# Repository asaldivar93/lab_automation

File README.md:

## PWM Channels

To control PWM channels you have to create an Output class instance for each channel. The board has up to 6 channels.

```C++
#define N_OUTPUTS 6

Output CH_0(0, PIN_CH0, "pwm", MANUAL, 0);
Output CH_1(1, PIN_CH1, "pwm", MANUAL, 0);
Output CH_2(2, PIN_CH2, "pwm", MANUAL, 0);
Output CH_3(3, PIN_CH3, "pwm", MANUAL, 0);
Output CH_4(4, PIN_CH4, "pwm", MANUAL, 0);
Output CH_5(5, PIN_CH5, "pwm", MANUAL, 0);
Output outputs[N_OUTPUTS] = {CH_0, CH_1, CH_2, CH_3, CH_4, CH_5};
```

Channels can be controled in 4 different modes: {MANUAL, TIMER, PID, ONOFF}. You can initialize this control mode through setter functions.

```C++
Output::set_manual_output(int value);
Output::set_timer(int time_on, int time_off, int value);
Output::set_pid(float *input_value, float setpoint);
Output::set_onoff(float *input_value, int lb, int ub, int value);
```

Example:

```C++
void setup(){
  ...
  outputs[2].set_timer(10, 60, 255);
  ...
}
```

Which is equivalent to doing this:

```C++
void setup(){
  ...
  CH_2.set_timer(10, 60, 255);
  ...
}
```

The PID and ONOFF setters expect a pointer to the measured variable:
```C++
void setup(){
  ...
  outputs[2].set_pid(&inputs[1].value, 50.5);
  outputs[3].set_pid(&inputs[3].value, 1, 1.5, 255);
  ...
}
```
### PID control

The PID controler has important parameters that need to be defined during MCU initialization. This parameters have default values:

- PWM_min_vaule = 0
- PWM_max_value = 255
- Sampling time in microseconds = 250000 (0.250s)
- PID constants:
  - Kp = 100, Ki = 0.2, Kd = 0.

The PID controler uses a simple g-h filter to smooth very noisy signals. The filter uses this formula:

```C++
filtered_input[k] = alpha * current_input + (1 - alpha) * filtered_input[k - 1]
```
where *alpha* [0, 1] controls the strength of the smoothing. *alpha* = 1 **no smoothing at all**, *alpha* close to 0 **very strongth smoothing**. By **default** *alpha* = 0.01.

The default values were tuned to control the temperature of a water reservoir using an external electrical resistance and have been tested to heat water volumes between 50mL and 2L.

These parameters are initialized through setter functions:

```C++
Output::set_sample_time_us(uint32_t sample_time_us);
Output::set_pid_tunings(float Kp, float Ki, float Kd);
Output::set_output_limits(float min, float max);
Output::set_gh_filter(float alpha);
```
example:

```C++
void setup(){
  ...
  outputs[2].set_sample_time_us(250000);
  outputs[2].set_pid_tunings(100, 0.2, 0.);
  outputs[2].set_output_limits(0, 240);
  outputs[2].set_gh_filter(0.01);
  outputs[2].set_pid(&inputs[1].value, 50.5);
  ...
}
```

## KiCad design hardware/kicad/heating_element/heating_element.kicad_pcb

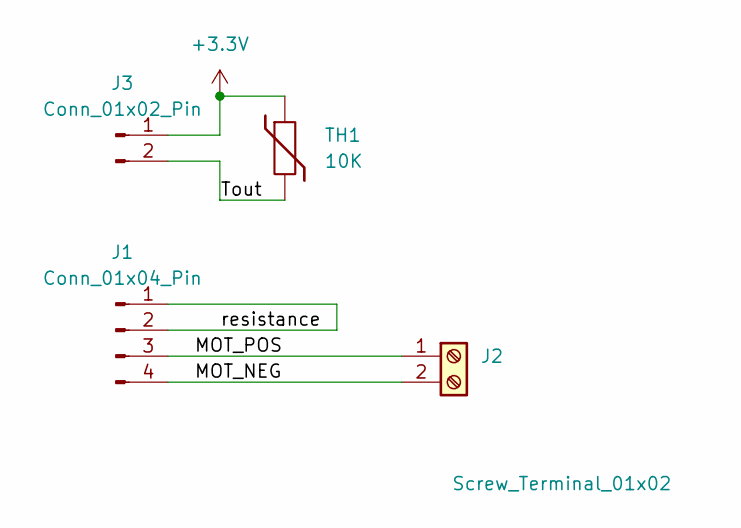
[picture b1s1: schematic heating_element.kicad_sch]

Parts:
J1: Conn_01x04_Pin; PinHeader_1x04_P2.54mm_Vertical
J2: Screw_Terminal_01x02; TerminalBlock_Phoenix_PT-1,5-2-5.0-H_1x02_P5.00mm_Horizontal
J3: Conn_01x02_Pin; PinHeader_1x02_P2.54mm_Vertical
TH1: 10K; R_Axial_DIN0204_L3.6mm_D1.6mm_P1.90mm_Vertical

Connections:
+3.3V: J3.1, TH1.1
/MOT_NEG: J1.4, J2.2
/MOT_POS: J1.3, J2.1
/Tout: J3.2, TH1.2
/resistance: J1.1, J1.2

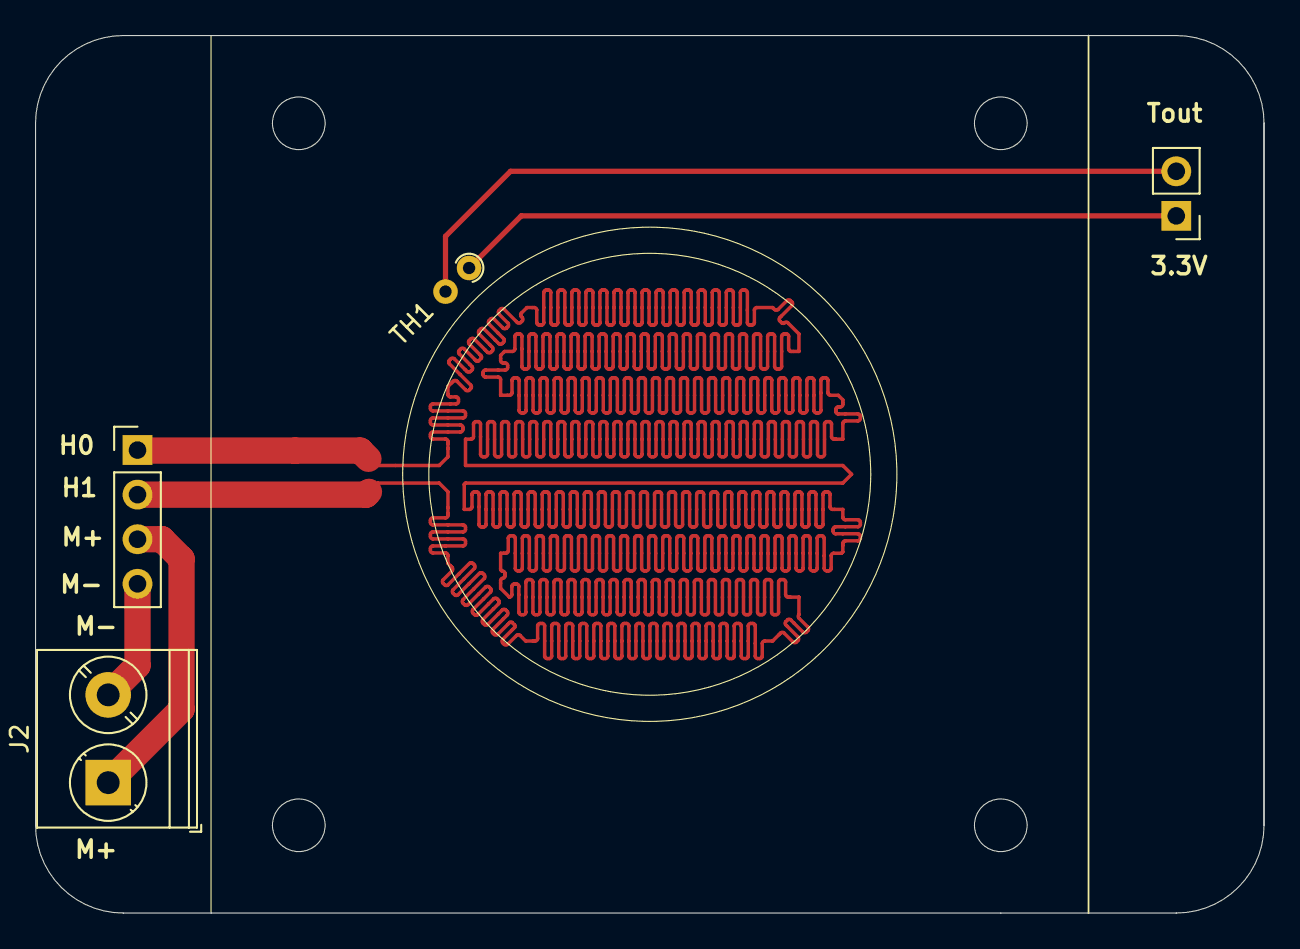
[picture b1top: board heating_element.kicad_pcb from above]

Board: 2 copper layers, 70.0 x 50.0 mm, 4 parts (0 on the bottom side), 5 nets.

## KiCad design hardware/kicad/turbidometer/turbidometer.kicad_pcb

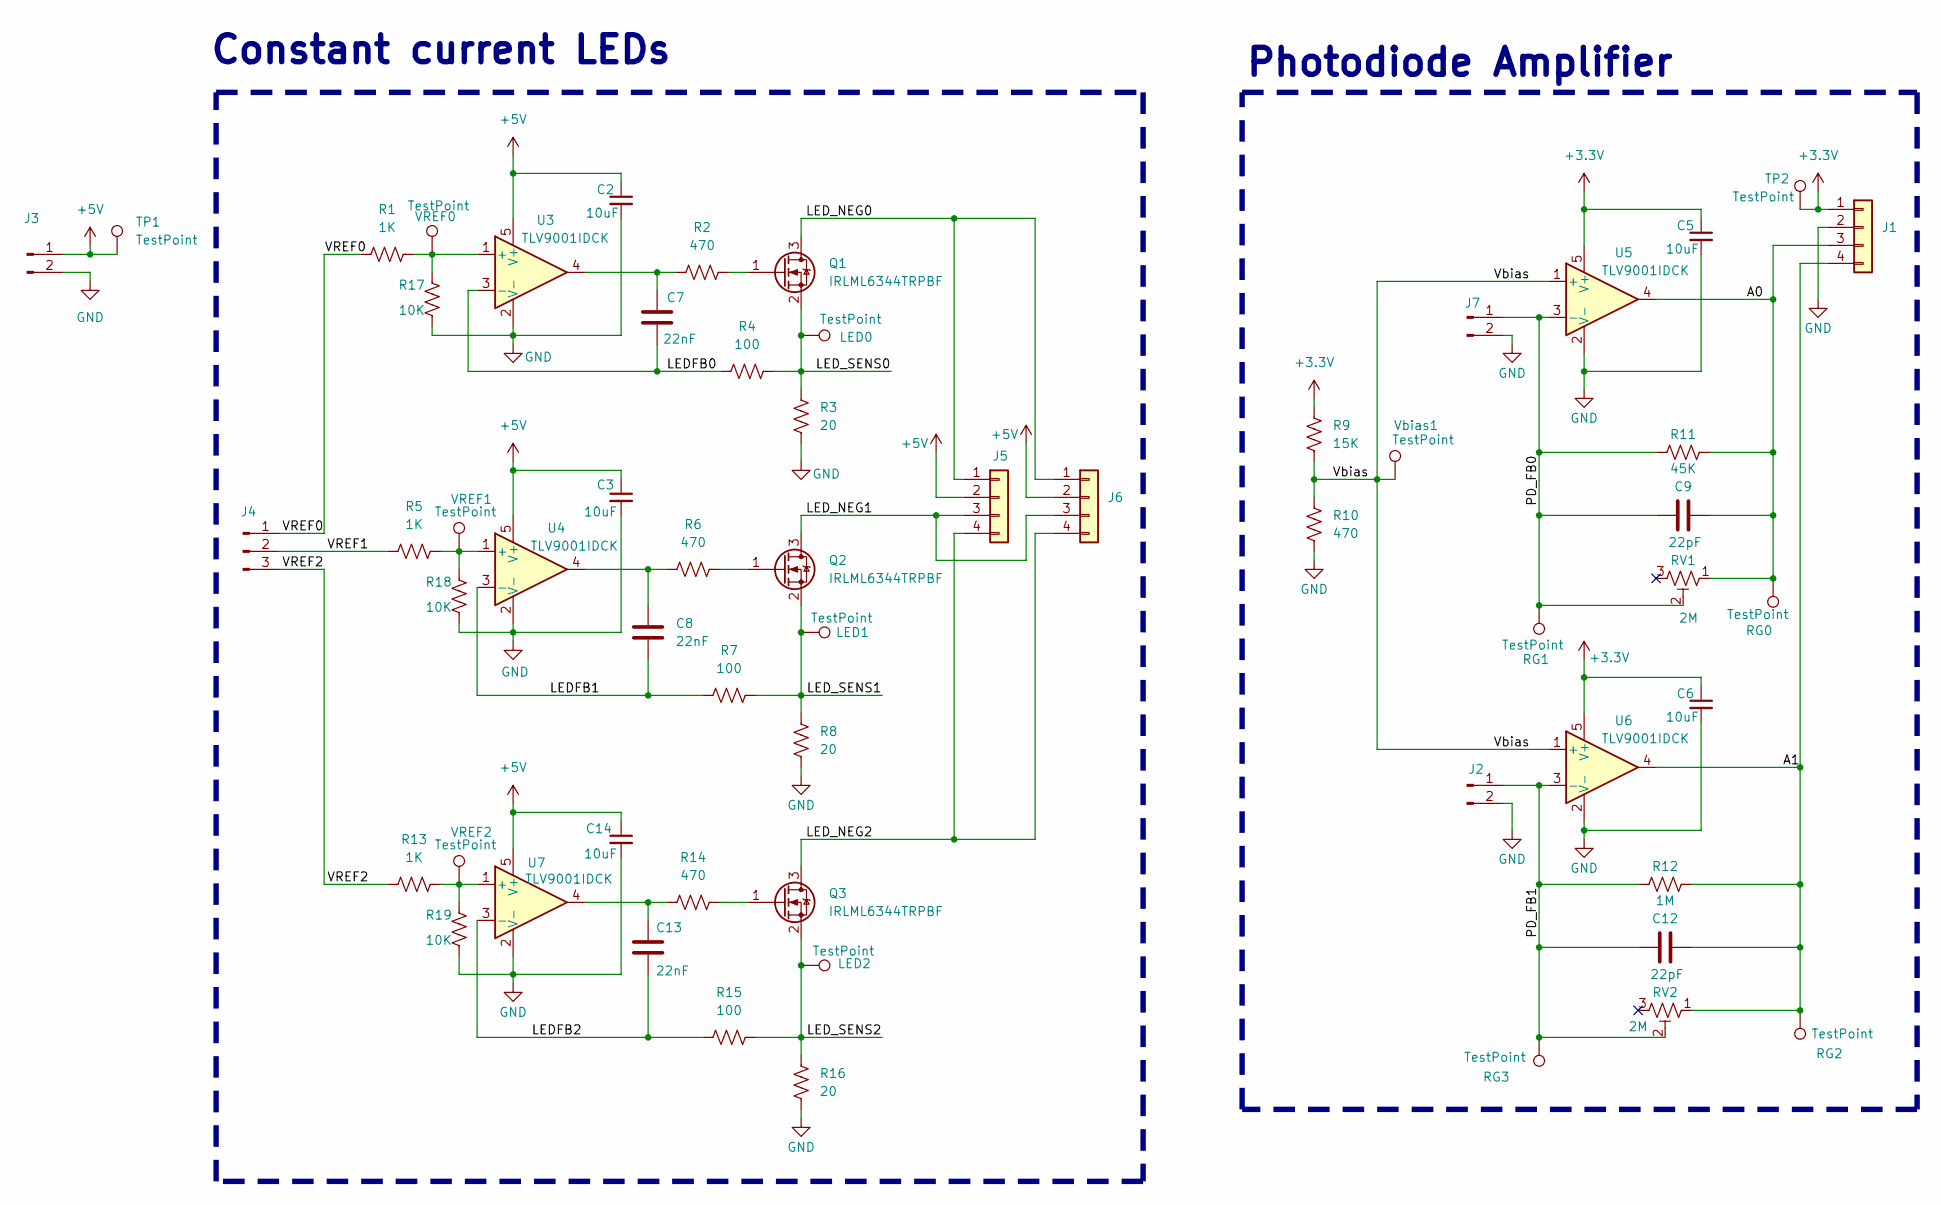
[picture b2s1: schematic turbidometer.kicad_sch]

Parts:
C2, C3, C5, C6, C14: 10uF; C_0805_2012Metric_Pad1.18x1.45mm_HandSolder
C7, C8, C13: 22nF; C_0805_2012Metric_Pad1.18x1.45mm_HandSolder
C9, C12: 22pF; C_0805_2012Metric_Pad1.18x1.45mm_HandSolder
J1: Conn_01x04; PinHeader_1x04_P2.54mm_Vertical
J2, J7: Conn_01x02_Pin; PinSocket_1x02_P2.54mm_Vertical
J3: Conn_01x02_Pin; PinHeader_1x02_P2.54mm_Vertical
J4: Conn_01x03_Pin; PinHeader_1x03_P2.54mm_Vertical
J5, J6: Conn_01x04; PinSocket_1x04_P2.54mm_Vertical
LED0, LED1, LED2: TestPoint; TestPoint_THTPad_1.5x1.5mm_Drill0.7mm
Q1, Q2, Q3: IRLML6344TRPBF; SOT-23_Handsoldering
R1, R5, R13: 1K; R_0805_2012Metric_Pad1.20x1.40mm_HandSolder
R2, R6, R10, R14: 470; R_0805_2012Metric_Pad1.20x1.40mm_HandSolder
R3, R8, R16: 20; R_0805_2012Metric_Pad1.20x1.40mm_HandSolder
R4, R7, R15: 100; R_0805_2012Metric_Pad1.20x1.40mm_HandSolder
R9: 15K; R_0805_2012Metric_Pad1.20x1.40mm_HandSolder
R11: 45K; R_0805_2012Metric_Pad1.20x1.40mm_HandSolder
R12: 1M; R_0805_2012Metric_Pad1.20x1.40mm_HandSolder
R17, R18, R19: 10K; R_0805_2012Metric_Pad1.20x1.40mm_HandSolder
RG0, RG1, RG2, RG3: TestPoint; TestPoint_THTPad_1.5x1.5mm_Drill0.7mm
RV1, RV2: 2M; Potentiometer_Bourns_3214W_Vertical
TP1, TP2: TestPoint; TestPoint_Pad_1.0x1.0mm
U3, U4, U5, U6, U7: TLV9001IDCK; SOT-353_SC-70-5
VREF0, VREF1, VREF2: TestPoint; TestPoint_THTPad_1.5x1.5mm_Drill0.7mm
Vbias1: TestPoint; TestPoint_Pad_1.0x1.0mm

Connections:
+3.3V: C5.1, C6.1, J1.1, R9.1, TP2.1, U5.5 (V+), U6.5 (V+)
+5V: C2.1, C3.1, C14.1, J3.1, J5.2, J6.2, TP1.1, U3.5 (V+), U4.5 (V+), U7.5 (V+)
/A0: C9.2, J1.3, R11.1, RG0.1, RV1.1, U5.4
/A1: C12.2, J1.4, R12.1, RG2.1, RV2.1, U6.4
/LEDFB0: C7.2, R4.2, U3.3 (-)
/LEDFB1: C8.2, R7.2, U4.3 (-)
/LEDFB2: C13.2, R15.2, U7.3 (-)
/LED_NEG0: J5.1, J6.1, Q1.3 (D)
/LED_NEG1: J5.3, J6.3, Q2.3 (D)
/LED_NEG2: J5.4, J6.4, Q3.3 (D)
/LED_SENS0: LED0.1, Q1.2 (S), R3.1, R4.1
/LED_SENS1: LED1.1, Q2.2 (S), R7.1, R8.1
/LED_SENS2: LED2.1, Q3.2 (S), R15.1, R16.1
/PD_FB0: C9.1, J7.1, R11.2, RG1.1, RV1.2, U5.3 (-)
/PD_FB1: C12.1, J2.1, R12.2, RG3.1, RV2.2, U6.3 (-)
/VREF0: J4.1, R1.2
/VREF1: J4.2, R5.2
/VREF2: J4.3, R13.2
/Vbias: R9.2, R10.1, U5.1 (+), U6.1 (+), Vbias1.1
GND: C2.2, C3.2, C5.2, C6.2, C14.2, J1.2, J2.2, J3.2, J7.2, R3.2, R8.2, R10.2, R16.2, R17.2, R18.2, R19.2, U3.2 (V-), U4.2 (V-), U5.2 (V-), U6.2 (V-), U7.2 (V-)
unnamed: C7.1, R2.2, U3.4
unnamed: C8.1, R6.2, U4.4
unnamed: C13.1, R14.2, U7.4
unnamed: Q1.1 (G), R2.1
unnamed: Q2.1 (G), R6.1
unnamed: Q3.1 (G), R14.1
unnamed: R1.1, R17.1, U3.1 (+), VREF0.1
unnamed: R5.1, R18.1, U4.1 (+), VREF1.1
unnamed: R13.1, R19.1, U7.1 (+), VREF2.1

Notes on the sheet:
Constant current LEDs
Photodiode Amplifier

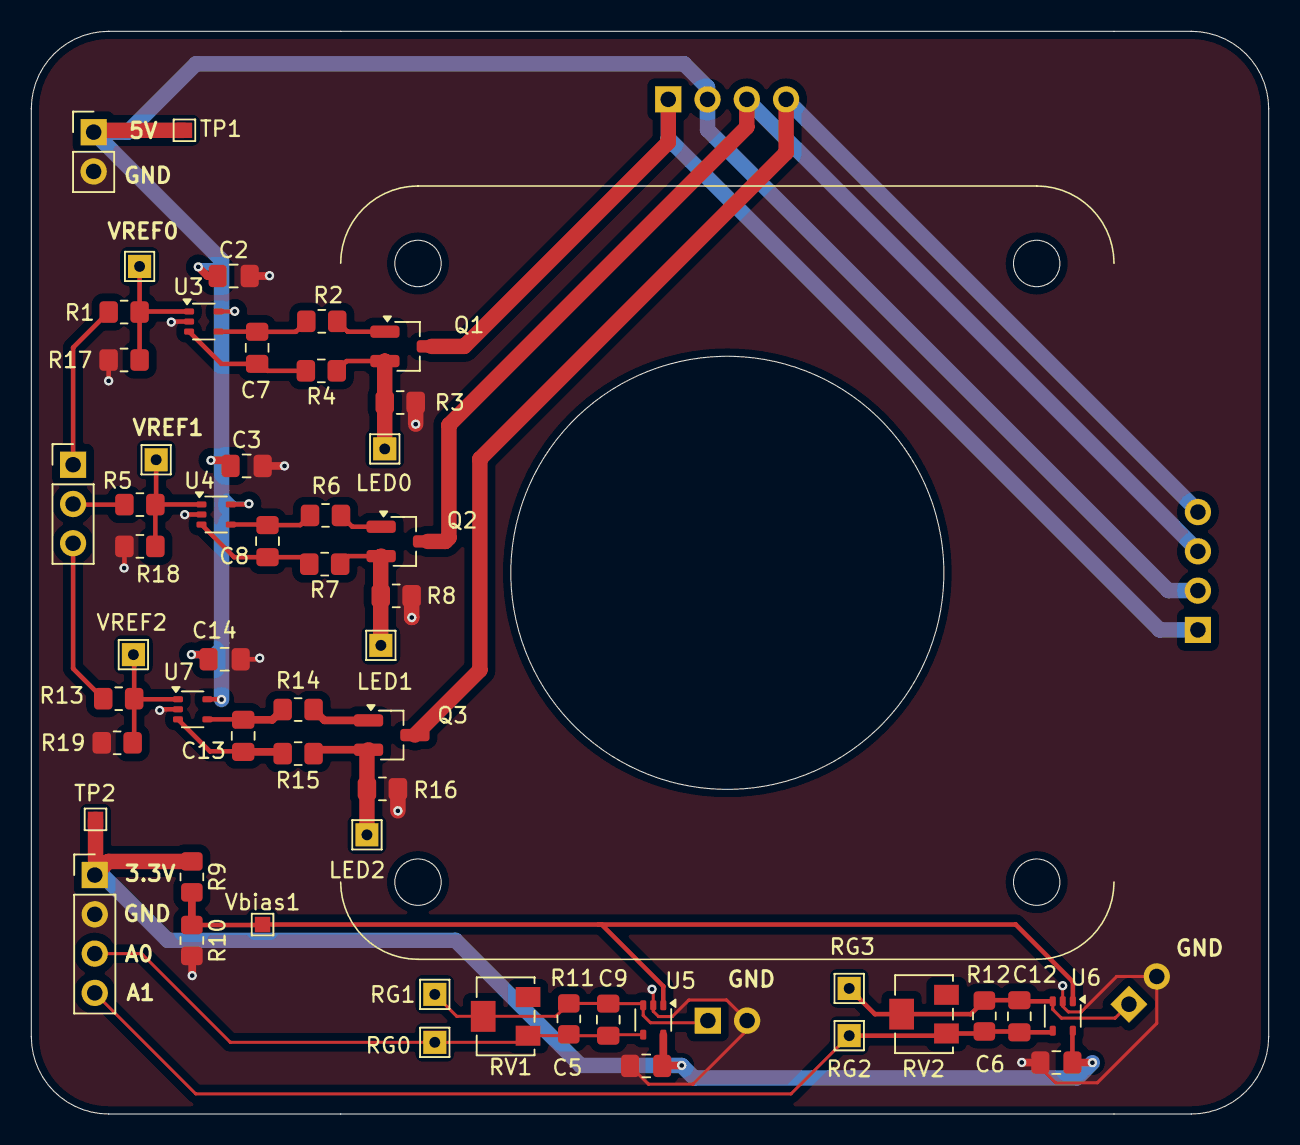
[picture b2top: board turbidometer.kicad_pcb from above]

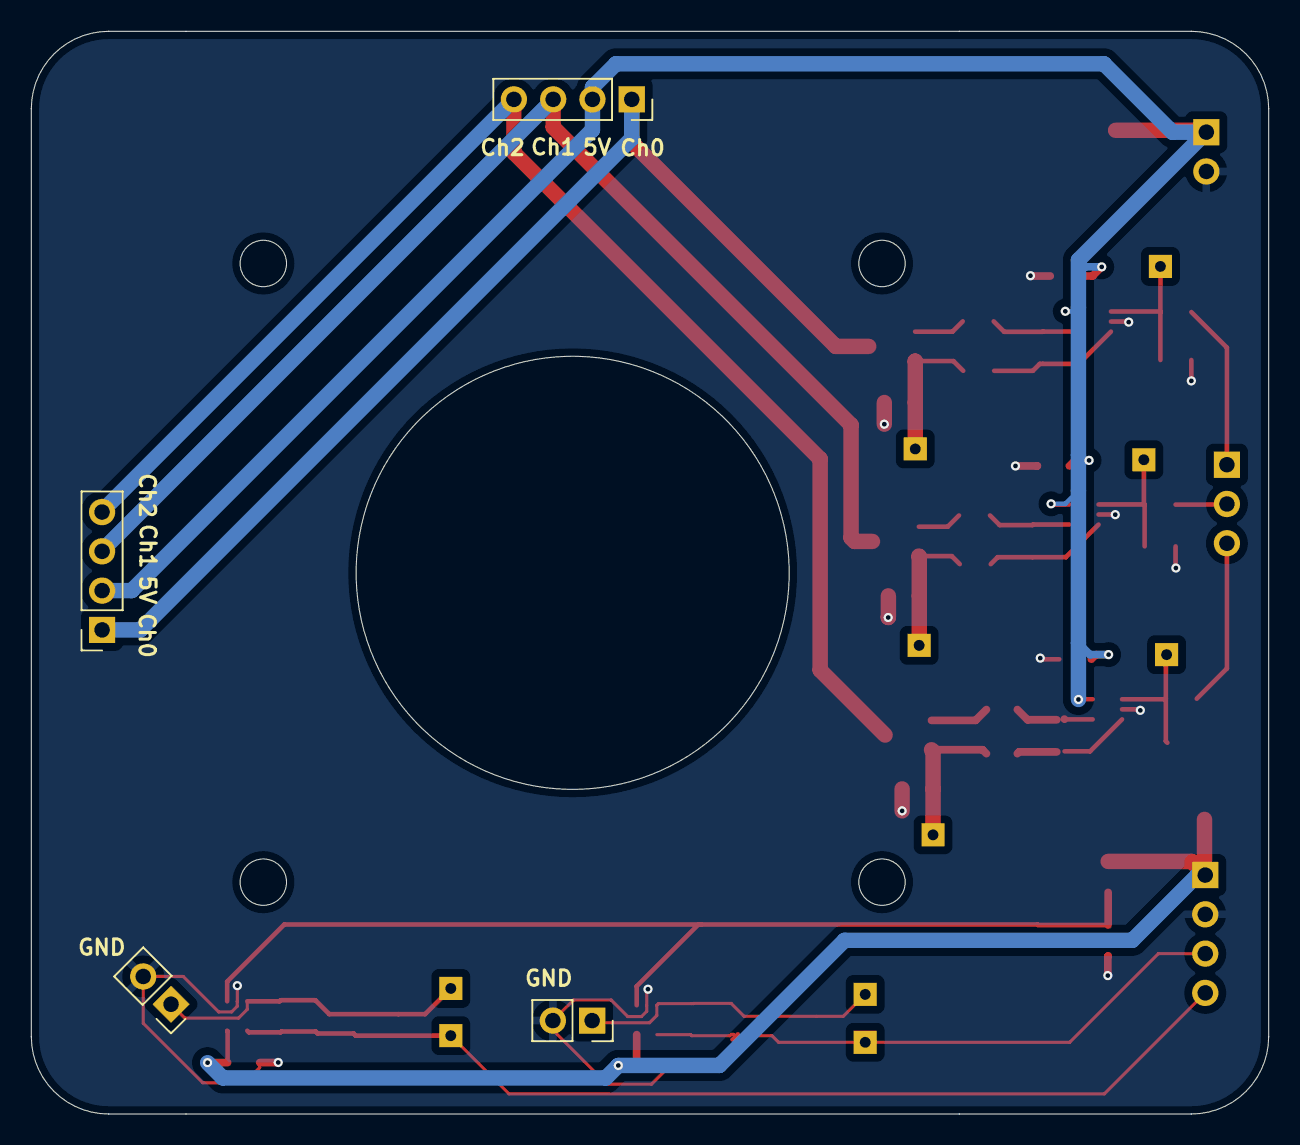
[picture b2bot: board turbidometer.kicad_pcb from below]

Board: 2 copper layers, 80.0 x 70.0 mm, 59 parts (4 on the bottom side), 29 nets.

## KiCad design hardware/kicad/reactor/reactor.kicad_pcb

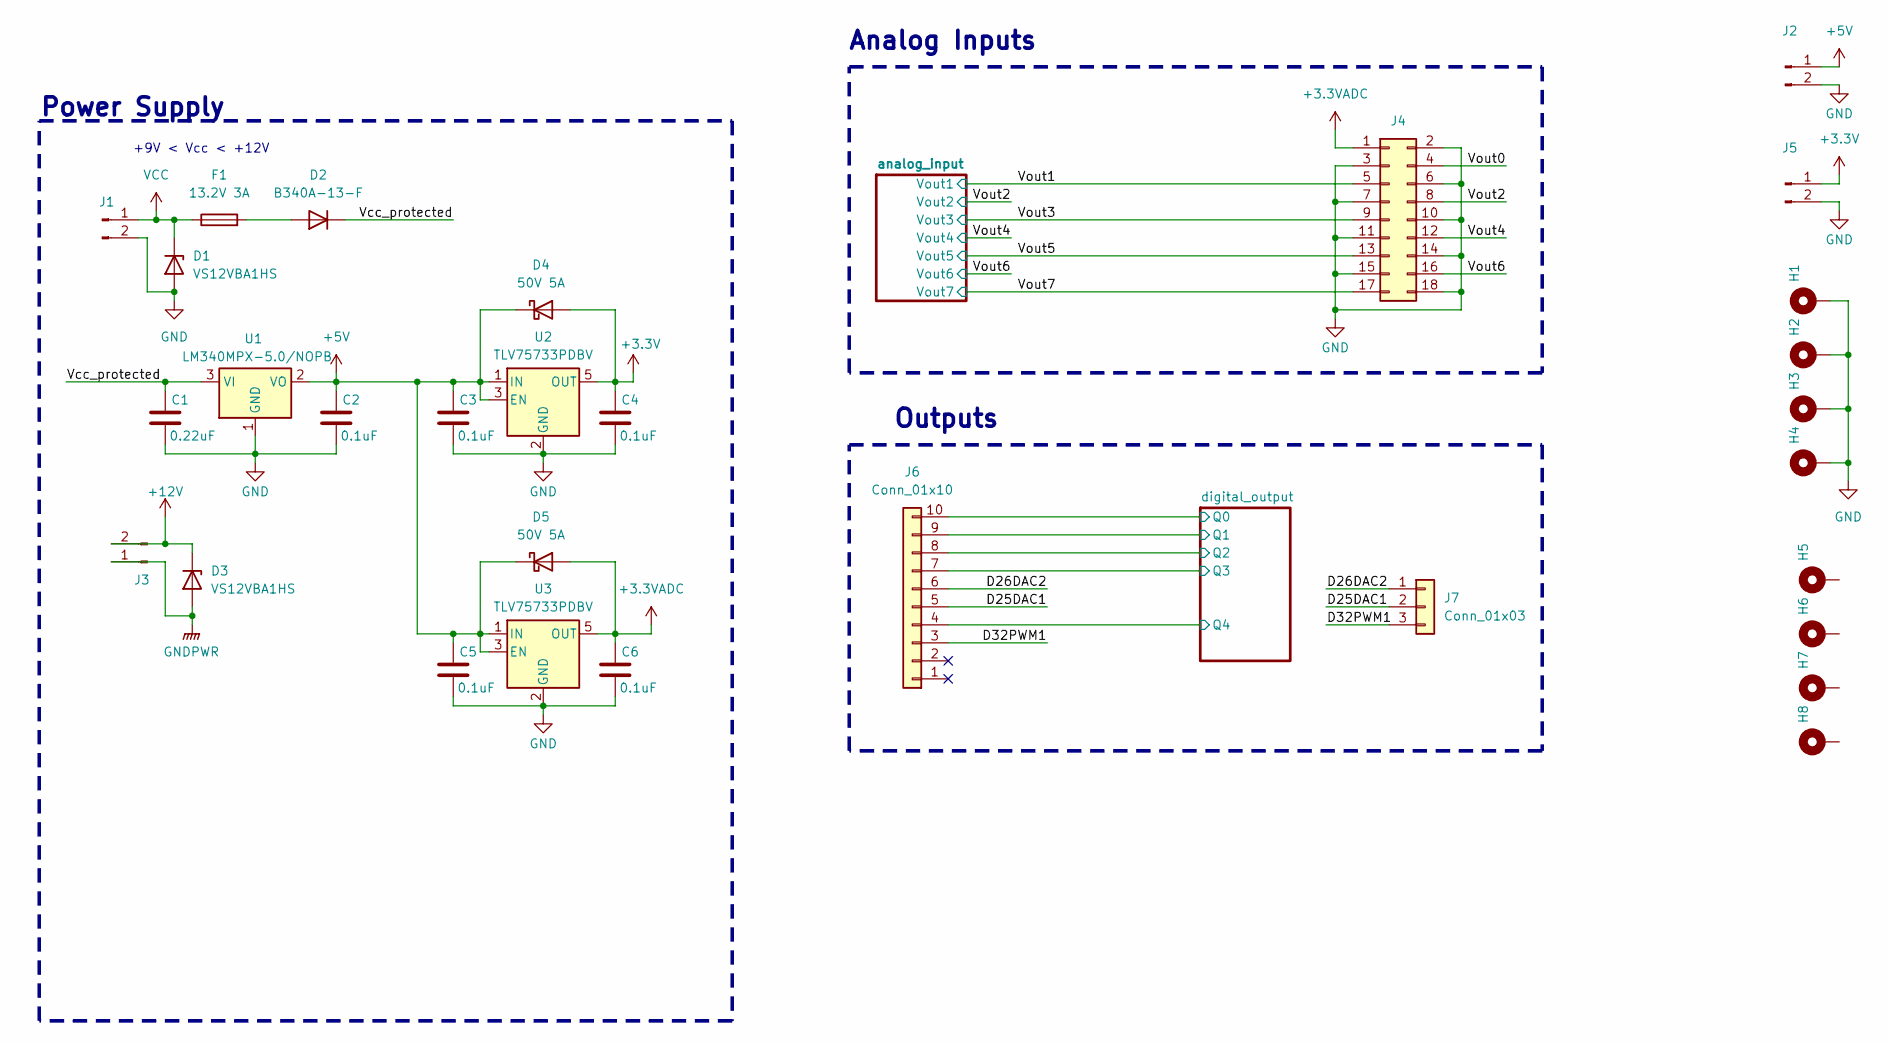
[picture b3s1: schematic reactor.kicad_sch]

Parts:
C1: 0.22uF; C_0805_2012Metric_Pad1.18x1.45mm_HandSolder
C2, C3, C4, C5, C6: 0.1uF; C_1206_3216Metric
D1, D3: VS12VBA1HS; D_0603_1608Metric_Pad1.05x0.95mm_HandSolder
D2: B340A-13-F; D_SMA
D4, D5: 50V 5A; D_SMA
F1: 13.2V 3A; Fuse_1206_3216Metric
H1, H2, H3, H4, H5, H6, H7, H8: MountingHole_Pad; MountingHole_3.2mm_M3_DIN965_Pad_TopBottom
J1, J2: Conn_01x02_Pin; PhoenixContact_MC_1,5_2-G-3.81_1x02_P3.81mm_Horizontal
J3: Conn_01x02_Pin; AMASS_XT60-F_1x02_P7.20mm_Vertical
J4: Conn_02x09_Odd_Even; PinSocket_2x09_P2.54mm_Vertical
J5: Conn_01x02_Pin; PinSocket_1x02_P2.54mm_Vertical
J6: Conn_01x10; PinSocket_1x10_P2.54mm_Vertical
J7: Conn_01x03; PhoenixContact_MC_1,5_3-G-3.81_1x03_P3.81mm_Horizontal
U1: LM340MPX-5.0/NOPB; SOT-223-3_TabPin2
U2, U3: TLV75733PDBV; SOT-23-5

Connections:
+3.3V: C4.1, D4.2 (A), J5.1, U2.5 (OUT)
+3.3VADC: C6.1, D5.2 (A), J4.1, U3.5 (OUT); also elsewhere on the board
+5V: C2.1, C3.1, C5.1, D4.1 (K), D5.1 (K), J2.1, U1.2 (VO), U2.1 (IN), U2.3 (EN), U3.1 (IN), U3.3 (EN)
+12V: D3.1 (K), J3.2; also elsewhere on the board
/D25DAC1: J6.5, J7.2
/D26DAC2: J6.6, J7.1
/D32PWM1: J6.3, J7.3
/Vcc_protected: C1.1, D2.1 (K), U1.3 (VI)
/Vout0: J4.4
/Vout1: J4.5; also elsewhere on the board
/Vout2: J4.8; also elsewhere on the board
/Vout3: J4.9; also elsewhere on the board
/Vout4: J4.12; also elsewhere on the board
/Vout5: J4.13; also elsewhere on the board
/Vout6: J4.16; also elsewhere on the board
/Vout7: J4.17; also elsewhere on the board
/digital_output/Q0: J6.10; also elsewhere on the board
/digital_output/Q1: J6.9; also elsewhere on the board
/digital_output/Q2: J6.8; also elsewhere on the board
/digital_output/Q3: J6.7; also elsewhere on the board
/digital_output/Q4: J6.4; also elsewhere on the board
GND: C1.2, C2.2, C3.2, C4.2, C5.2, C6.2, D1.2 (A), H1.1, H2.1, H3.1, H4.1, J1.2, J2.2, J4.2, J4.3, J4.6, J4.7, J4.10, J4.11, J4.14, J4.15, J4.18, J5.2, U1.1 (GND), U2.2 (GND), U3.2 (GND); also elsewhere on the board
GNDPWR: D3.2 (A), J3.1; also elsewhere on the board
unnamed: D2.2 (A), F1.2
VCC: D1.1 (K), F1.1, J1.1

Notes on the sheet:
Outputs
+9V < Vcc < +12V
Analog Inputs
Power Supply

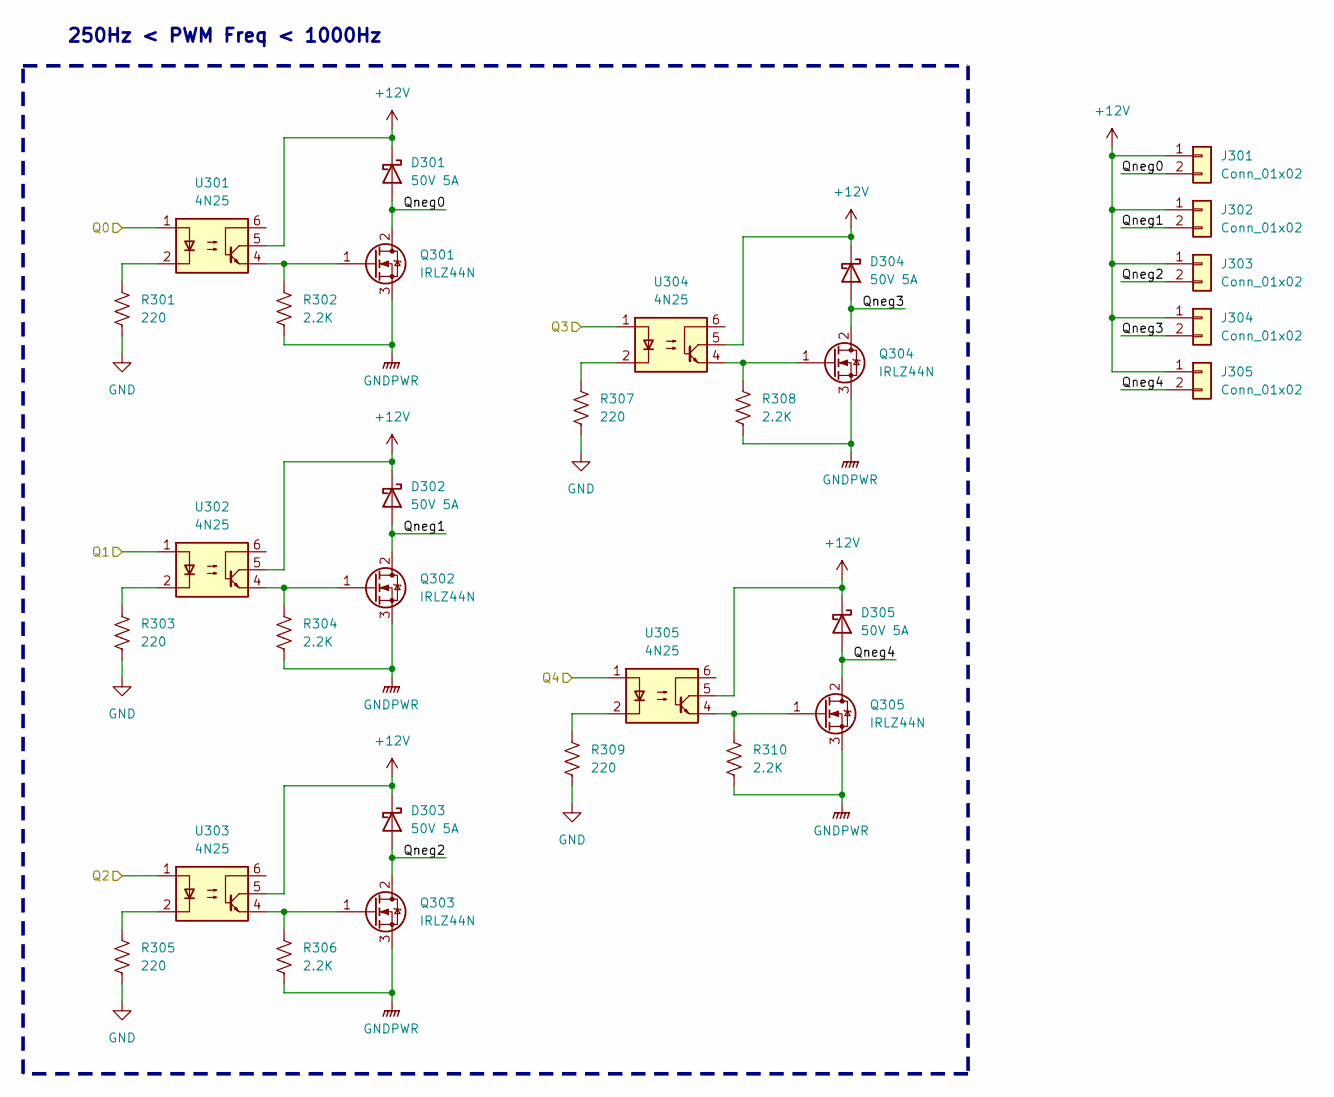
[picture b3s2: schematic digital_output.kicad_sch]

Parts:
D301, D302, D303, D304, D305: 50V 5A; D_SMA_Handsoldering
J301, J302, J303, J304, J305: Conn_01x02; PhoenixContact_MC_1,5_2-G-3.81_1x02_P3.81mm_Horizontal
Q301, Q302, Q303, Q304, Q305: IRLZ44N; TO-220-3_Vertical
R301, R303, R305, R307, R309: 220; R_Axial_DIN0204_L3.6mm_D1.6mm_P5.08mm_Horizontal
R302, R304, R306, R308, R310: 2.2K; R_Axial_DIN0204_L3.6mm_D1.6mm_P5.08mm_Horizontal
U301, U302, U303, U304, U305: 4N25; DIP-6_W7.62mm_Socket

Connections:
+12V: D301.1 (K), D302.1 (K), D303.1 (K), D304.1 (K), D305.1 (K), J301.1, J302.1, J303.1, J304.1, J305.1, U301.5, U302.5, U303.5, U304.5, U305.5; also elsewhere on the board
/digital_output/Q0: U301.1; also elsewhere on the board
/digital_output/Q1: U302.1; also elsewhere on the board
/digital_output/Q2: U303.1; also elsewhere on the board
/digital_output/Q3: U304.1; also elsewhere on the board
/digital_output/Q4: U305.1; also elsewhere on the board
/digital_output/Qneg0: D301.2 (A), J301.2, Q301.2 (D)
/digital_output/Qneg1: D302.2 (A), J302.2, Q302.2 (D)
/digital_output/Qneg2: D303.2 (A), J303.2, Q303.2 (D)
/digital_output/Qneg3: D304.2 (A), J304.2, Q304.2 (D)
/digital_output/Qneg4: D305.2 (A), J305.2, Q305.2 (D)
GND: R301.2, R303.2, R305.2, R307.2, R309.2; also elsewhere on the board
GNDPWR: Q301.3 (S), Q302.3 (S), Q303.3 (S), Q304.3 (S), Q305.3 (S), R302.2, R304.2, R306.2, R308.2, R310.2; also elsewhere on the board
unnamed: Q301.1 (G), R302.1, U301.4
unnamed: Q302.1 (G), R304.1, U302.4
unnamed: Q303.1 (G), R306.1, U303.4
unnamed: Q304.1 (G), R308.1, U304.4
unnamed: Q305.1 (G), R310.1, U305.4
unnamed: R301.1, U301.2
unnamed: R303.1, U302.2
unnamed: R305.1, U303.2
unnamed: R307.1, U304.2
unnamed: R309.1, U305.2

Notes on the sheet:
250Hz < PWM Freq < 1000Hz

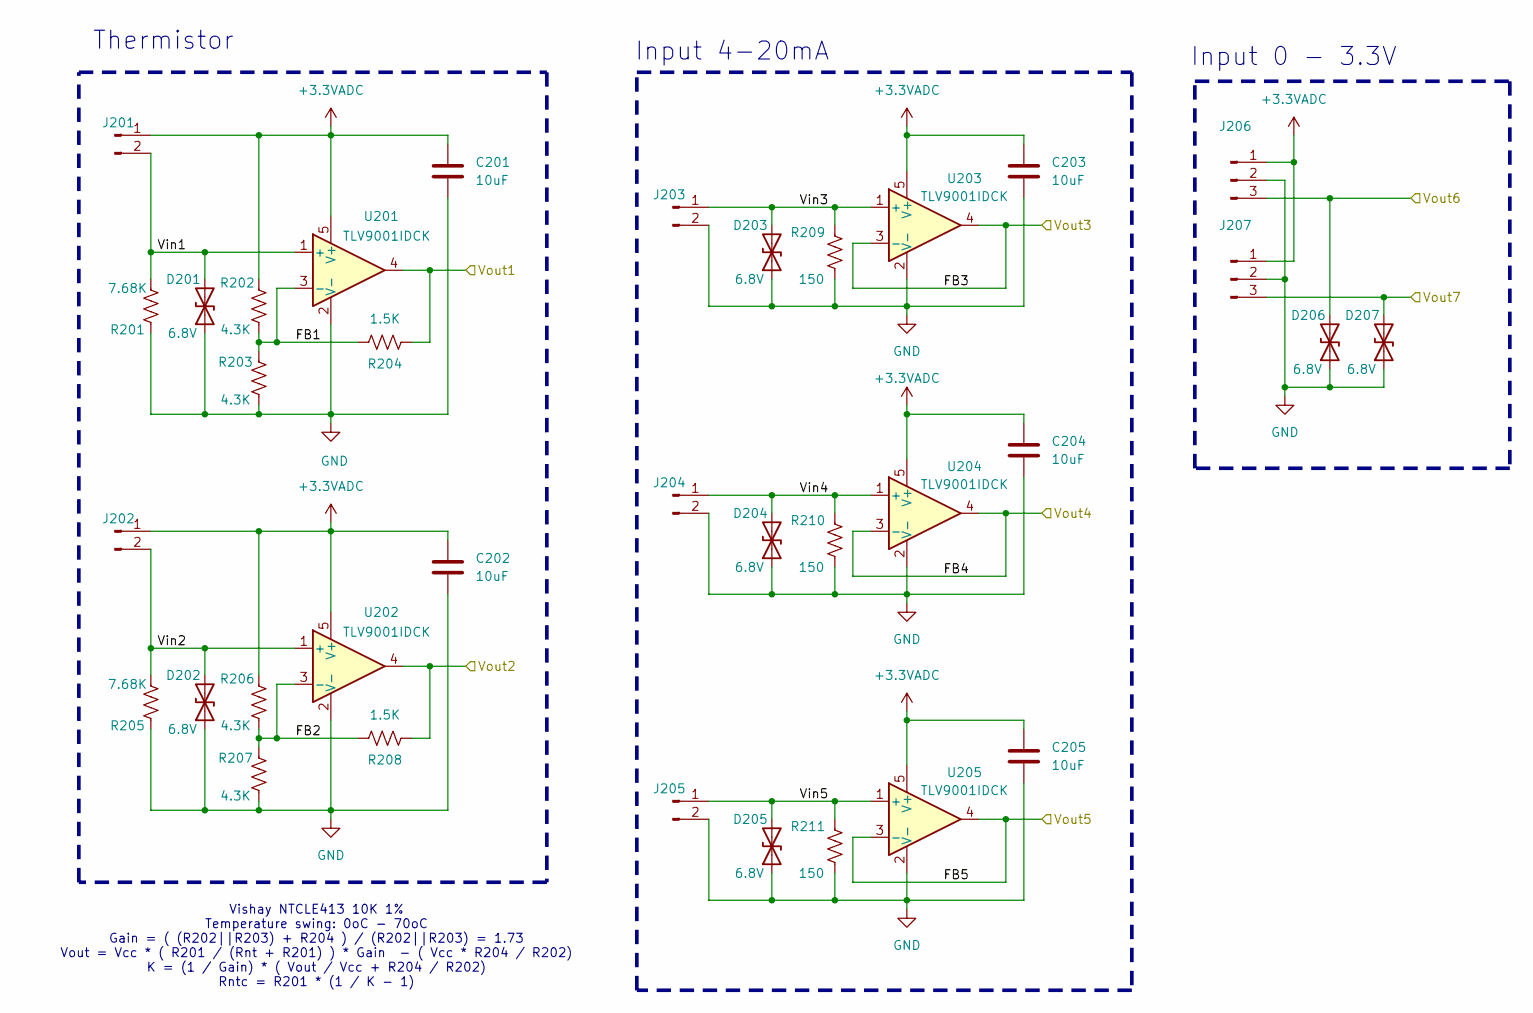
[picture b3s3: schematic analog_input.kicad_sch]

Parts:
C201, C202, C203, C204, C205: 10uF; C_0805_2012Metric_Pad1.18x1.45mm_HandSolder
D201, D202, D203, D204, D205, D206, D207: 6.8V; D_SOD-523
J201, J202, J203, J204, J205: Conn_01x02_Pin; PhoenixContact_MC_1,5_2-G-3.81_1x02_P3.81mm_Horizontal
J206, J207: Conn_01x03_Pin; PhoenixContact_MC_1,5_3-G-3.81_1x03_P3.81mm_Horizontal
R201, R205: 7.68K; R_0805_2012Metric_Pad1.20x1.40mm_HandSolder
R202, R203, R206, R207: 4.3K; R_0805_2012Metric_Pad1.20x1.40mm_HandSolder
R204, R208: 1.5K; R_0805_2012Metric_Pad1.20x1.40mm_HandSolder
R209, R210, R211: 150; R_0805_2012Metric_Pad1.20x1.40mm_HandSolder
U201, U202, U203, U204, U205: TLV9001IDCK; SOT-353_SC-70-5

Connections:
+3.3VADC: C201.1, C202.1, C203.1, C204.1, C205.1, J201.1, J202.1, J206.1, J207.1, R202.2, R206.2, U201.5 (V+), U202.5 (V+), U203.5 (V+), U204.5 (V+), U205.5 (V+); also elsewhere on the board
/Vout1: R204.2, U201.4; also elsewhere on the board
/Vout2: R208.2, U202.4; also elsewhere on the board
/Vout3: U203.3 (-), U203.4; also elsewhere on the board
/Vout4: U204.3 (-), U204.4; also elsewhere on the board
/Vout5: U205.3 (-), U205.4; also elsewhere on the board
/Vout6: D206.2 (A2), J206.3; also elsewhere on the board
/Vout7: D207.2 (A2), J207.3; also elsewhere on the board
/analog_input/FB1: R202.1, R203.2, R204.1, U201.3 (-)
/analog_input/FB2: R206.1, R207.2, R208.1, U202.3 (-)
/analog_input/Vin1: D201.2 (A2), J201.2, R201.2, U201.1 (+)
/analog_input/Vin2: D202.2 (A2), J202.2, R205.2, U202.1 (+)
/analog_input/Vin3: D203.2 (A2), J203.1, R209.2, U203.1 (+)
/analog_input/Vin4: D204.2 (A2), J204.1, R210.2, U204.1 (+)
/analog_input/Vin5: D205.2 (A2), J205.1, R211.2, U205.1 (+)
GND: C201.2, C202.2, C203.2, C204.2, C205.2, D201.1 (A1), D202.1 (A1), D203.1 (A1), D204.1 (A1), D205.1 (A1), D206.1 (A1), D207.1 (A1), J203.2, J204.2, J205.2, J206.2, J207.2, R201.1, R203.1, R205.1, R207.1, R209.1, R210.1, R211.1, U201.2 (V-), U202.2 (V-), U203.2 (V-), U204.2 (V-), U205.2 (V-); also elsewhere on the board

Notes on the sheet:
Vishay NTCLE413 10K 1% Temperature swing: 0oC - 70oC Gain = ( (R202||R203) + R204 ) / (R202||R203) = 1.73 Vout = Vcc * ( R201 / (Rnt + R201) ) * Gain - ( Vcc * R204 / R202) K = (1 / Gain) * ( Vout / Vcc + R204 / R202) Rntc = R201 * (1 / K - 1)
Input 4-20mA
Input 0 - 3.3V
Thermistor

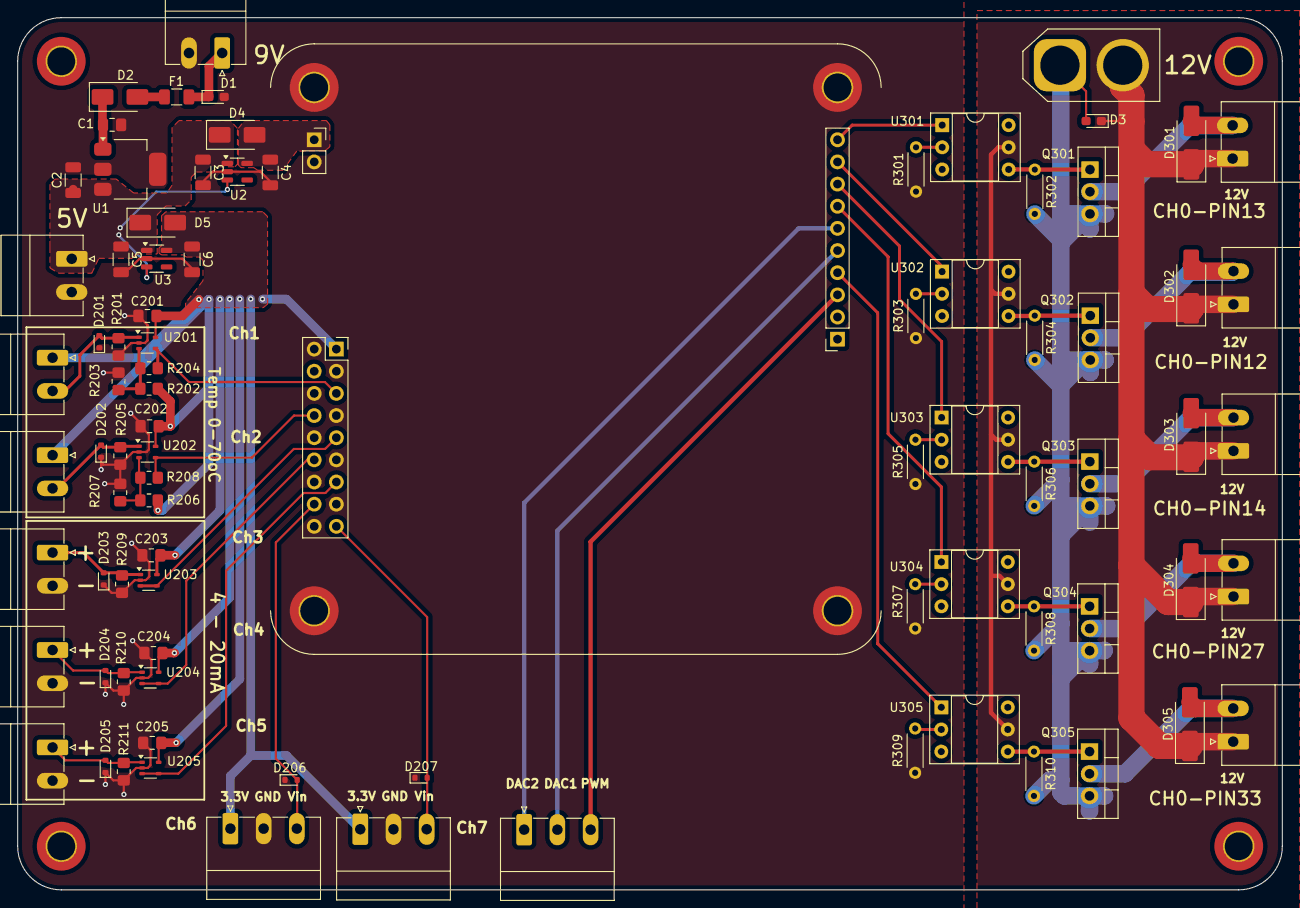
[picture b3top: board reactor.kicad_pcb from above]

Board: 2 copper layers, 145.0 x 100.0 mm, 95 parts (0 on the bottom side), 46 nets.
